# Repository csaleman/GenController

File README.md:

# Westinghouse Generator Controller

This controller is based on csvanholmPicoW design, thank you Carsten!
## What makes this design different? 
- Designed to be used with Home Assistant, however shouldn't be difficult to make is an standalone WebUI like in Joe Hershberger's implementation.
- Outage detection is done using the battery tender. Thus, this only works if you have an ATS with subpanel like mine [Nature's Generator 50A ATS](https://naturesgenerator.com/products/50a-automatic-generator-transfer-switch) which I highly recommend instead of a full house ATS that would restore the battery tender. A future version might include an option for a external dry contact.   
- ESP32 based, specifically SEEED Studio XIAO ESP-32-C3, there are multiple pin compatible modules, they are easy to get from Seeedstudio, Amazon, Digikey, Mouser etc. I would recommend the ESP32-C3 or C6 just for the external antenna connection.

## Hardware
- GX20 - 7 Pins

# References:
 - [Reddit Custom Controller Build](https://www.reddit.com/r/OffGrid/comments/mxygik/westinghouse_generator_automatic_transfer_switch/)
 - [csvanholm/WestinghousePicoW](https://github.com/csvanholm/WestinghousePicoW)
 - [jhershbe/westinghouse-smart-switch-adapter](https://github.com/jhershbe/westinghouse-smart-switch-adapter)

# Help Requested
If you have an iGEN11000tfc or iGEN12000tfc, can you please measure the voltage between pin 5 and 6 and let me know? My generator just has 1.8V ac between those pins while running in idle, so it is too low for the bridge rectifier and optoisolator.

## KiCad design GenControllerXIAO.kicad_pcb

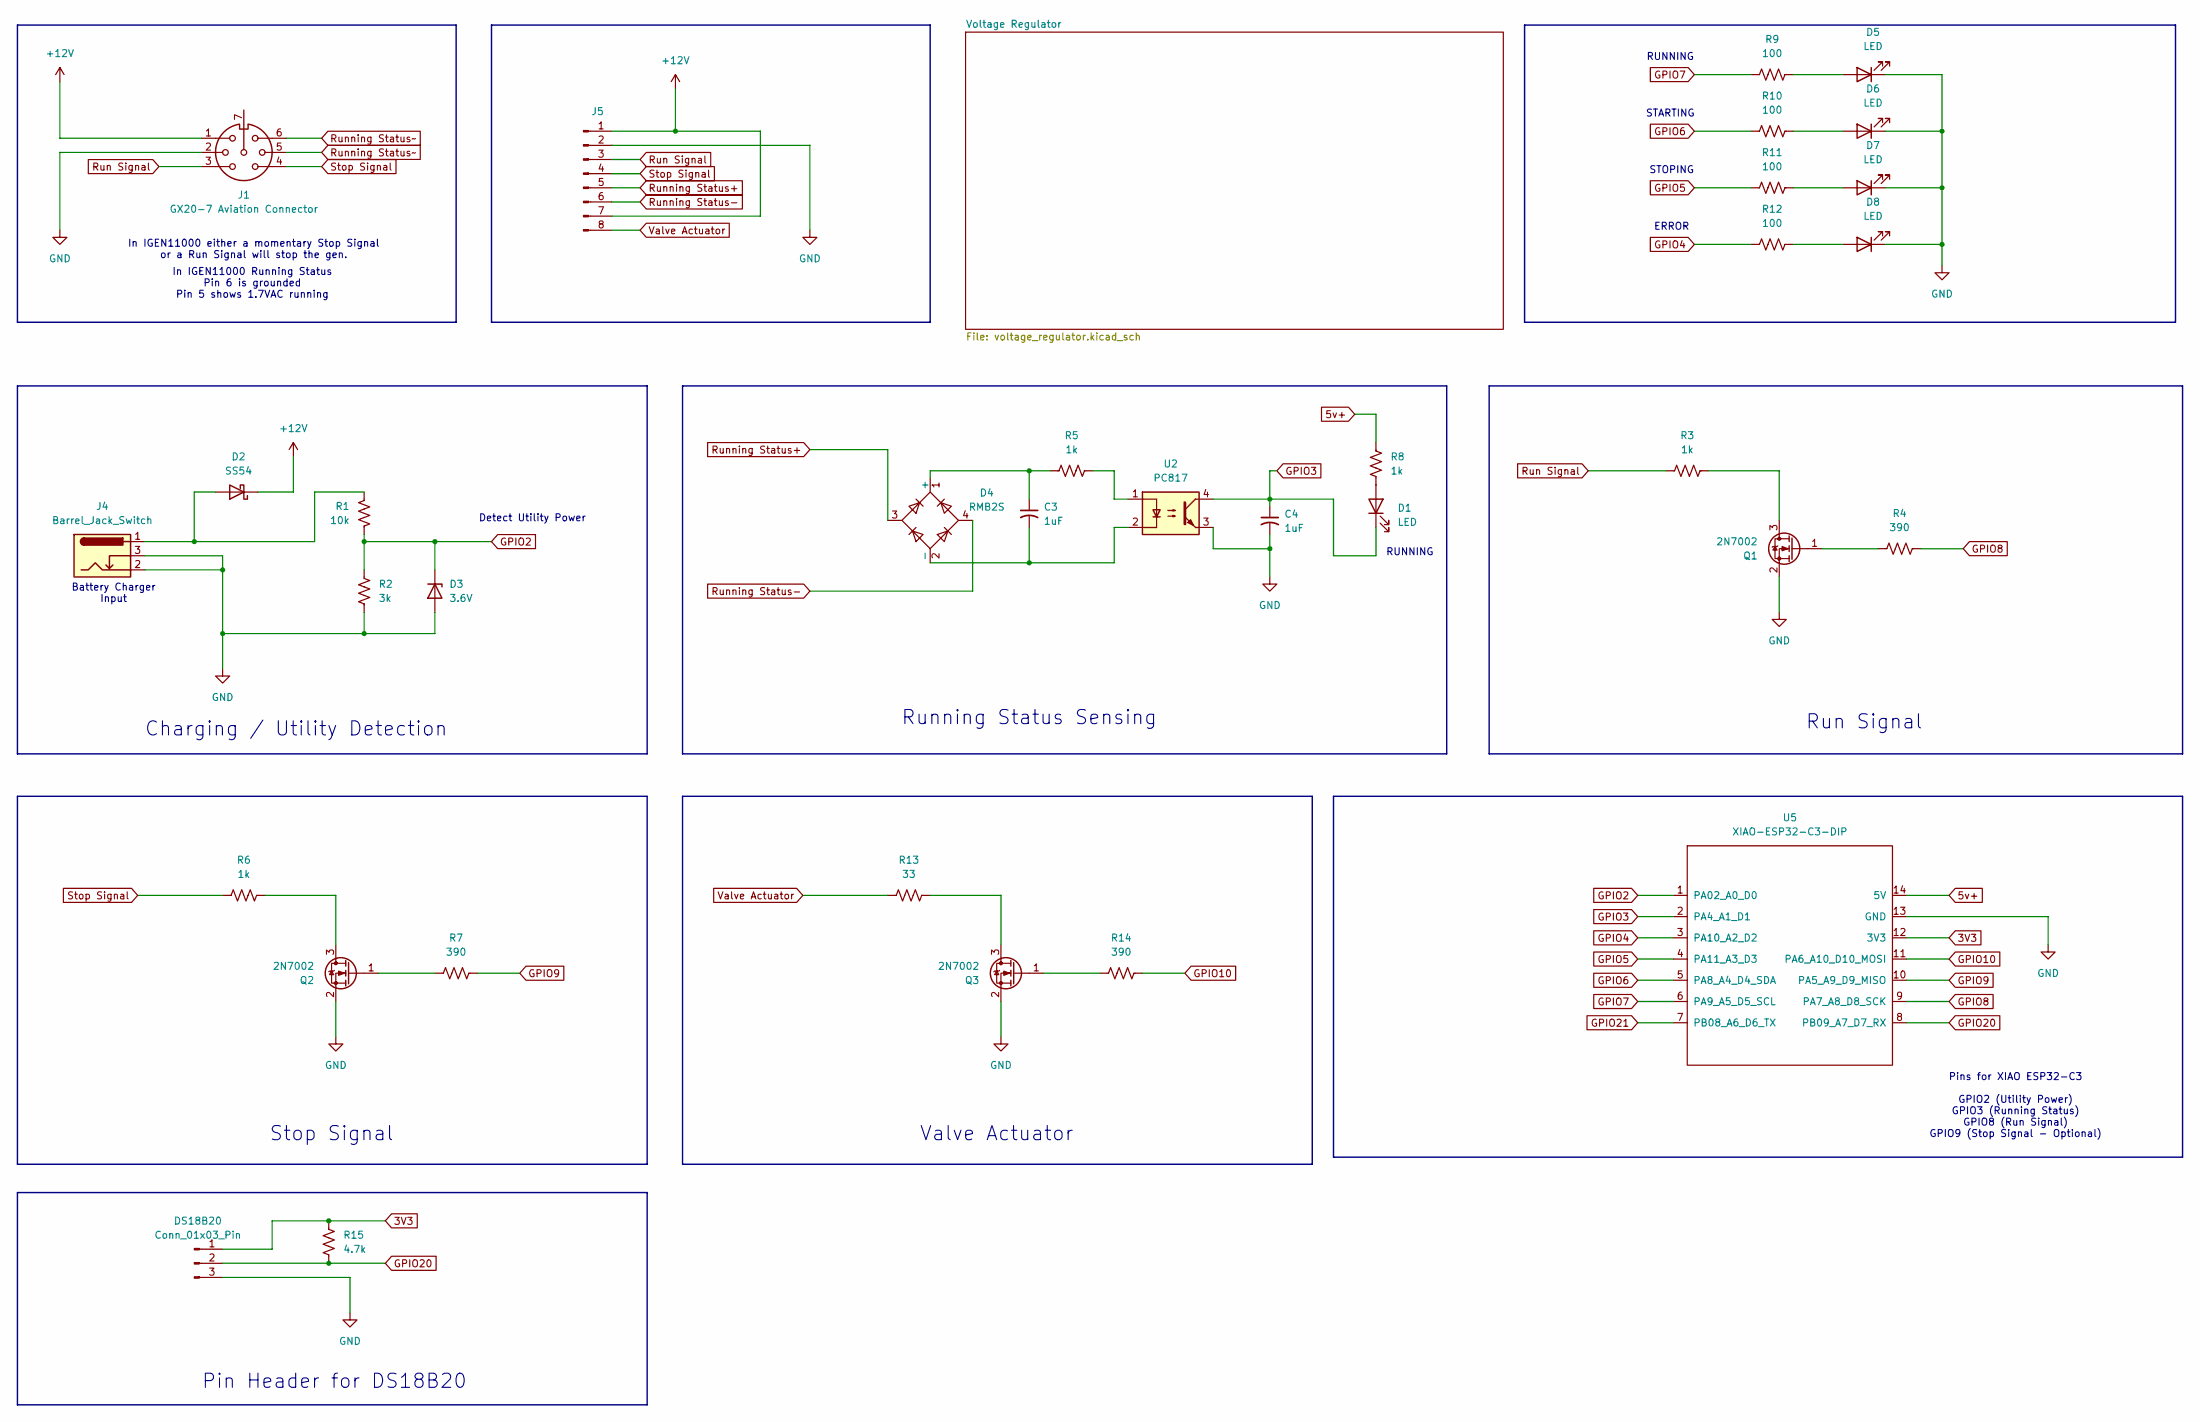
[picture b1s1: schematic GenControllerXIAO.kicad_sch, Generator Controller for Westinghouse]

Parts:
C3, C4: 1uF; C_0805_2012Metric_Pad1.18x1.45mm_HandSolder; JLCP Part# C28323
D1, D5, D6, D7, D8: LED; LED_0603_1608Metric_Pad1.05x0.95mm_HandSolder; LCSC Part # C2286
D2: SS54; D_SMA; LCSC Part # C22452
D3: 3.6V; D_SOD-123; LCSC Part # C726991
D4: RMB2S; TO-269AA; LCSC Part # C2488
DS18B20: Conn_01x03_Pin; PinHeader_1x03_P2.54mm_Vertical
J1: GX20-7 Aviation Connector
J4: Barrel_Jack_Switch; BarrelJack_GCT_DCJ200-10-A_Horizontal
J5: Conn_01x08_Pin; TerminalBlock_Phoenix_MPT-0,5-8-2.54_1x08_P2.54mm_Horizontal
Q1, Q2, Q3: 2N7002; SOT-23; LCSC Part # C8545
R1: 10k; R_0805_2012Metric; LCSC Part # C17414
R2: 3k; R_0805_2012Metric; LCSC Part # C17661
R3, R5, R6, R8: 1k; R_0805_2012Metric; LCSC Part # C17513
R4, R7, R14: 390; R_0805_2012Metric; LCSC Part # C17655
R9, R10, R11, R12: 100; LED_0805_2012Metric_Pad1.15x1.40mm_HandSolder; LCSC Part # C17408
R13: 33; R_0805_2012Metric; LCSC Part # C17634
R15: 4.7k; R_0805_2012Metric; LCSC Part # C17673
U2: PC817; SMDIP-4_W9.53mm; LCSC Part # C109227
U5: XIAO-ESP32-C3-DIP

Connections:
3V3: DS18B20.1, R15.1, U5.12 (3V3)
5v+: R8.2, U5.14 (5V); also elsewhere on the board
+12V: D2.1 (K), J1.1, J5.1, J5.7; also elsewhere on the board
GND: C4.2, D3.2 (A), D5.1 (K), D6.1 (K), D7.1 (K), D8.1 (K), DS18B20.3, J1.2, J4.2, J4.3, J5.2, Q1.2 (S), Q2.2 (S), Q3.2 (S), R2.2, U2.3, U5.13 (GND); also elsewhere on the board
GPIO2: D3.1 (K), R1.2, R2.1, U5.1 (PA02_A0_D0)
GPIO3: C4.1, D1.1 (K), U2.4, U5.2 (PA4_A1_D1)
GPIO4: R12.1, U5.3 (PA10_A2_D2)
GPIO5: R11.1, U5.4 (PA11_A3_D3)
GPIO6: R10.1, U5.5 (PA8_A4_D4_SDA)
GPIO7: R9.1, U5.6 (PA9_A5_D5_SCL)
GPIO8: R4.2, U5.9 (PA7_A8_D8_SCK)
GPIO9: R7.2, U5.10 (PA5_A9_D9_MISO)
GPIO10: R14.2, U5.11 (PA6_A10_D10_MOSI)
GPIO20: DS18B20.2, R15.2, U5.8 (PB09_A7_D7_RX)
GPIO21: U5.7 (PB08_A6_D6_TX)
unnamed: D1.2 (A), R8.1
unnamed: D2.2 (A), J4.1, R1.1
unnamed: C3.1, D4.1 (+), R5.1
unnamed: C3.2, D4.2 (-), U2.2
unnamed: D5.2 (A), R9.2
unnamed: D6.2 (A), R10.2
unnamed: D7.2 (A), R11.2
unnamed: D8.2 (A), R12.2
unnamed: J1.5, J1.6
unnamed: Q1.3 (D), R3.2
unnamed: Q1.1 (G), R4.1
unnamed: Q2.3 (D), R6.2
unnamed: Q2.1 (G), R7.1
unnamed: Q3.3 (D), R13.2
unnamed: Q3.1 (G), R14.1
unnamed: R5.2, U2.1
Run Signal: J1.3, J5.3, R3.1
Running Status+: D4.3, J5.5
Running Status-: D4.4, J5.6
Stop Signal: J1.4, J5.4, R6.1
Valve Actuator: J5.8, R13.1

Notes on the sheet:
Detect Utility Power
RUNNING
In IGEN11000 either a momentary Stop Signal or a Run Signal will stop the gen.
Pin Header for DS18B20
ERROR
STARTING
Charging / Utility Detection
STOPING
Running Status Sensing
Run Signal
Battery Charger Input
In IGEN11000 Running Status Pin 6 is grounded Pin 5 shows 1.7VAC running
Stop Signal
Valve Actuator
Pins for XIAO ESP32-C3 GPIO2 (Utility Power) GPIO3 (Running Status) GPIO8 (Run Signal) GPIO9 (Stop Signal - Optional)

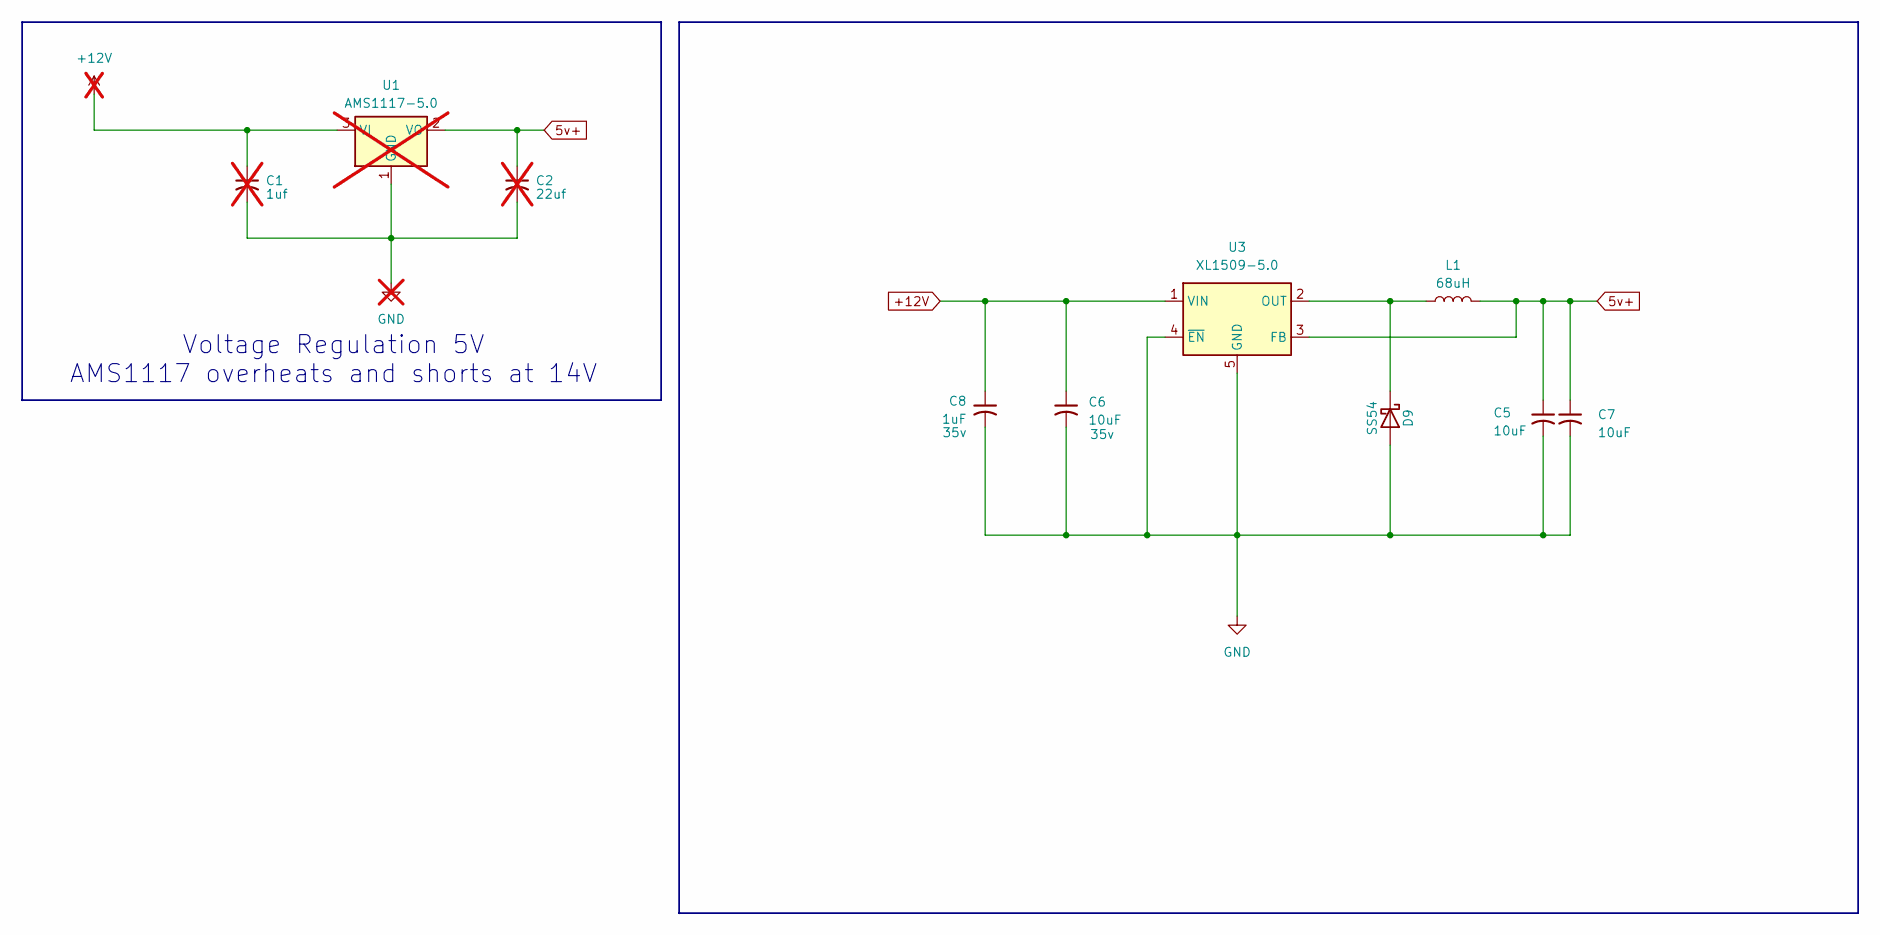
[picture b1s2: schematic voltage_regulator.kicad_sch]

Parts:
C1: 1uf; C_1206_3216Metric; LCSC Part # C1848; not fitted
C2: 22uf; C_1206_3216Metric; LCSC Part # C12891; not fitted
C5, C7: 10uF; C_0805_2012Metric_Pad1.18x1.45mm_HandSolder; LCSC Part # C440198
C6: 10uF; C_0805_2012Metric_Pad1.18x1.45mm_HandSolder; Voltage 35v; LCSC Part # C440198
C8: 1uF; C_0805_2012Metric_Pad1.18x1.45mm_HandSolder; Voltage 35v; JLCP Part# C28323
D9: SS54; D_SMA; LCSC Part # C22452
L1: 68uH; L_SXN_SMDRI127; LCSC Part # C9907
U1: AMS1117-5.0; SOT-223-3_TabPin2; LCSC Part # C6187; not fitted
U3: XL1509-5.0; SOIC-8_3.9x4.9mm_P1.27mm; LCSC Part # C61063

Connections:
5v+: C2.1, C5.1, C7.1, L1.2, U1.2 (VO), U3.3 (FB); also elsewhere on the board
+12V: C6.1, C8.1, U3.1 (VIN); also elsewhere on the board
GND: C1.2, C2.2, C5.2, C6.2, C7.2, C8.2, D9.2 (A), U1.1 (GND), U3.4 (~EN), U3.5 (GND), U3.6 (GND), U3.7 (GND), U3.8 (GND); also elsewhere on the board
unnamed: C1.1, U1.3 (VI)
unnamed: D9.1 (K), L1.1, U3.2 (OUT)

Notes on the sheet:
Voltage Regulation 5V AMS1117 overheats and shorts at 14V

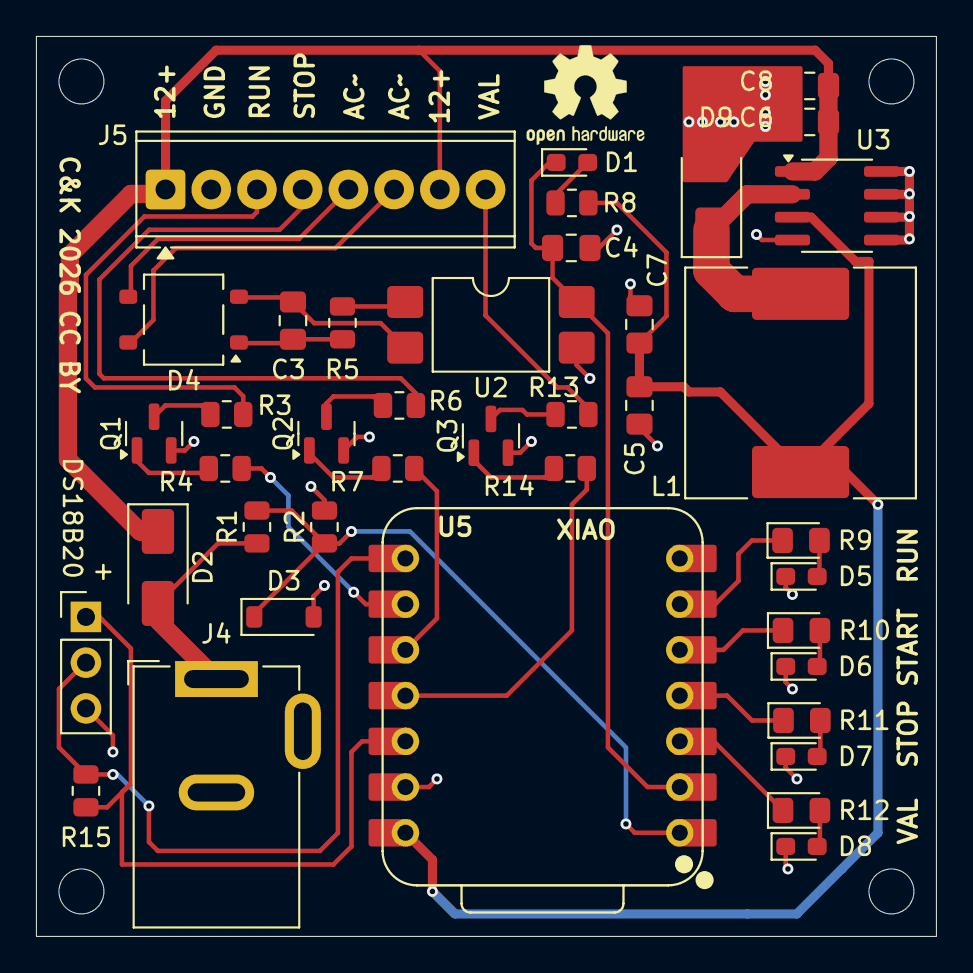
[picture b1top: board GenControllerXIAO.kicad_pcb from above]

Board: 2 copper layers, 50.0 x 50.0 mm, 40 parts (0 on the bottom side), 35 nets.

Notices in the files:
GenControllerXIAO.kicad_pcb:
C&K 2026 CC BY
